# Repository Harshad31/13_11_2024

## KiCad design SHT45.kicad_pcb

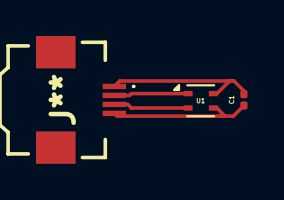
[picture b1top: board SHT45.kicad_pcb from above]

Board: 2 copper layers, 3 parts (0 on the bottom side), 4 nets.

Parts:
C1: 100nF; C_0201_0603Metric
J**: FFC2B3504T
U1: SHT4x; Sensirion_DFN-4_1.5x1.5mm_P0.8mm_SHT4x_NoCentralPad

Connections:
/GND: C1.2, J**.1, U1.4 (VSS)
/SCL: J**.3, U1.2 (SCL)
/SDA: J**.2, U1.1 (SDA)
/VDD: C1.1, J**.4, U1.3 (VDD)

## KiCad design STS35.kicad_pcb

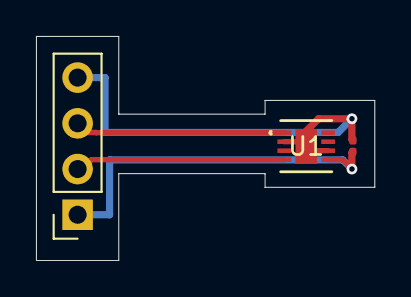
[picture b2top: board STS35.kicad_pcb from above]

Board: 2 copper layers, 18.8 x 12.4 mm, 3 parts (0 on the bottom side), 4 nets.

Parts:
C1: 100nF; C_0201_0603Metric
J2: Conn_01x04_Pin; PinSocket_1x04_P2.54mm_Vertical
U1: STS35-DIS; STS3x-DIS_SEN

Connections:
/GND: C1.2, J2.4, U1.2 (ADDR), U1.6 (NRESET), U1.9 (VSS)
/SCL: J2.2, U1.4 (SCL)
/SDA: J2.3, U1.1 (SDA)
/VDD3.3: C1.1, J2.1, U1.5 (VDD)

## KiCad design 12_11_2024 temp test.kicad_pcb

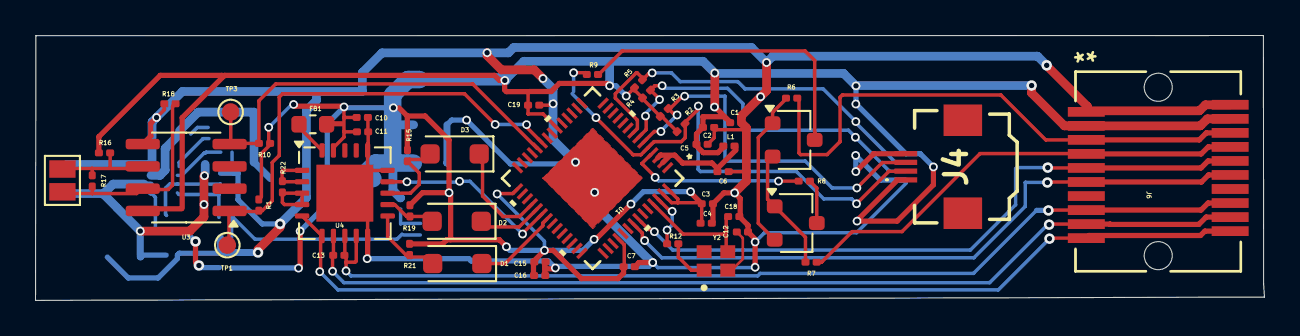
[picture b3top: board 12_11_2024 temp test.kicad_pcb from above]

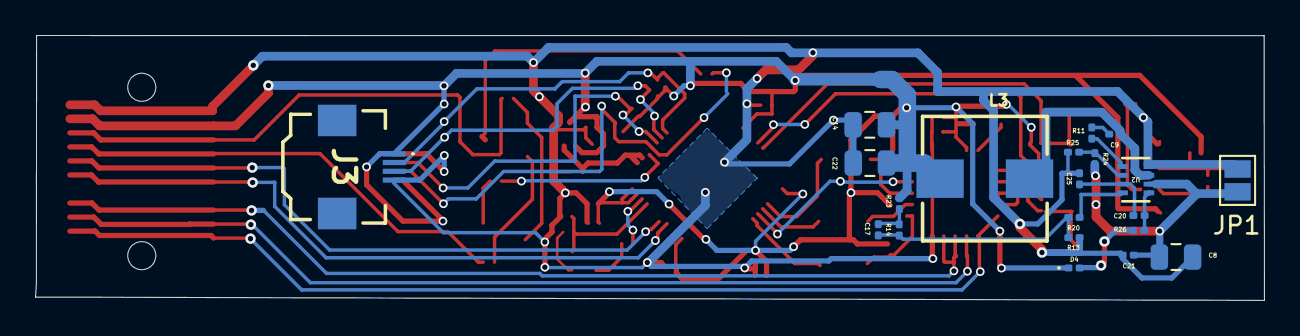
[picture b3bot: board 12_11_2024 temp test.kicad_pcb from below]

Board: 2 copper layers, 70.1 x 15.1 mm, 70 parts (21 on the bottom side), 47 nets.

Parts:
C1, C4, C13: 10uF; C_0201_0603Metric
C2, C3, C9, C16: 1uF; C_0201_0603Metric
C5, C6, C7, C10, C11, C12, C15, C18, C19: 0.1uF; C_0201_0603Metric
C8: 22uF(50V); C_0805_2012Metric
C14, C22: 22µF; C_0805_2012Metric
C17: 10pF; C_0201_0603Metric
C20: 1nF; C_0201_0603Metric
C21: 0.1uF(50V); C_0201_0603Metric
C25: 6.8nF; C_0201_0603Metric
D1, D2, D3: 1N4148W; D_SOD-123F
D4: LED; LED_0201_0603Metric
FB1: 470R; L_0603_1608Metric
J3, J4: FFC2B35-04-T; FFC2B3504T
J6: 10056847-101LF; CONN_10056847-101LF_AMP
JP1, JP2: SolderJumper_2_Open; SolderJumper-2_P1.3mm_Open_Pad1.0x1.5mm
L1: 2.0nH; L_0201_0603Metric
L3: 3.3µH; WE-HCI_7050
Q1, Q2: L8050QLT1G; SC-59
R1, R10: 10K; R_0201_0603Metric
R2, R3, R4, R5, R6, R7, R15, R19, R21: 10k; R_0201_0603Metric
R8, R9: 0R; R_0201_0603Metric
R11: 20R; R_0201_0603Metric
R12: 22R; R_0201_0603Metric
R13: 13K; R_0201_0603Metric
R14: 40.2K; R_0201_0603Metric
R16, R18: 20k; R_0201_0603Metric
R17: 120R; R_0201_0603Metric
R20: 20K; R_0201_0603Metric
R22: 400R; R_0201_0603Metric
R23: 10R; R_0201_0603Metric
R24: 1M; R_0201_0603Metric
R25: NC; R_0201_0603Metric
R26: 65R; R_0201_0603Metric
TP1, TP3: TestPoint; TestPoint_Pad_D1.0mm
U1: ESP32-S3FN8; ESP32 S3FN8_7X7_EXP-
U2: MP2393GTL-P; SOT583_MP2393
U3: THVD1420D; SOIC-8_3.9x4.9mm_P1.27mm
U4: MAX31865xTP; TQFN-20-1EP_5x5mm_P0.65mm_EP3.25x3.25mm
Y2: ECS-400-10-37B2-CKM-TR; XTAL_ECS-400-10-37B2-CKM-TR

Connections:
24V: C8.1, C21.1, JP1.2 (B), R24.1, U2.2 (IN)
/CHIP_PU: R8.2, U1.4 (CHIP_PU)
/CS: D3.1 (K), U1.32 (SPICS0)
/DTR: J6.4, J6.17, R7.1
/FORCE+: J6.10, J6.11, U4.5 (FORCE+), U4.6 (FORCE2)
/GPIO0: J4.2, R2.2, R9.2, U1.5 (GPIO0)
/MISO: U1.34 (SPIQ), U4.14 (SDO)
/MOSI: D1.1 (K), U1.35 (SPID)
/RTDN+: C13.1, J6.9, J6.12, U4.7 (RTDIN+)
/RTDN-: C13.2, J6.8, J6.13, U4.8 (RTDIN-), U4.9 (FORCE-)
/RTS: J6.3, J6.18, R6.1
/RX: J6.5, J6.16, U1.50 (U0RXD)
/RX1: R10.2, TP3.1, U1.24 (GPIO18), U3.4 (DI)
/SCL1: J3.3, R4.2, U1.7 (GPIO2)
/SCLK: D2.1 (K), U1.33 (SPICLK)
/SDA0: J4.3, R3.2, U1.6 (GPIO1)
/SDA1: J3.2, R5.2, U1.8 (GPIO3)
/TX: J6.6, J6.15, U1.49 (U0TXD)
/TX1: R1.2, TP1.1, U1.23 (GPIO17), U3.1 (RO)
/VDD3.3: C1.1, C2.1, C3.1, C4.1, C5.1, C6.1, C7.1, C10.1, C11.1, C14.1, C15.1, C16.1, C19.1, C22.1, D4.1 (K), FB1.1, J3.1, J4.1, J6.2, J6.19, L1.1, L1.2, L3.1, R1.1, R2.1, R3.1, R4.1, R5.1, R10.1, R15.1, R16.1, R19.1, R21.1, R23.1, U1.2 (VDD3P3), U1.3 (VDD3P3), U1.20 (VDD3P3_RTC), U1.29 (VDD_SPI), U1.46 (VDD3P3_CPU), U1.55 (VDDA), U1.56 (VDDA), U3.8 (VCC), U4.19 (DVDD)
/XTAL_N: C18.1, U1.53 (XTAL_N), Y2.3
/XTAL_P: R12.2, U1.54 (XTAL_P)
A: JP2.2 (B), R16.2, R17.1, U3.6 (A)
B: JP2.1 (A), R17.2, R18.1, U3.7 (B)
GND: C1.2, C2.2, C3.2, C4.2, C5.2, C6.2, C7.2, C8.2, C10.2, C11.2, C12.2, C14.2, C15.2, C16.2, C18.2, C19.2, C21.2, C22.2, C25.2, J3.4, J4.4, J6.1, J6.20, JP1.1 (A), R13.1, R18.2, R25.1, U1.57 (GND), U2.4 (GND), U3.5 (GND), U4.10 (GND), U4.15 (DGND), U4.16 (GND), U4.21 (GND)
unnamed: C9.1, R11.2
unnamed: C12.1, Y2.2
unnamed: C17.1, R13.2, R14.1, R20.2
unnamed: C17.2, R14.2, R23.2
unnamed: D1.2 (A), R21.2, U4.11 (SDI)
unnamed: D2.2 (A), R19.2, U4.12 (SCLK)
unnamed: D3.2 (A), R15.2, U4.13 (~CS)
unnamed: D4.2 (A), R26.1
unnamed: Q1.1, Q2.2, R7.2
unnamed: Q1.2, Q2.1, R6.2
unnamed: Q1.3, R8.1
unnamed: Q2.3, R9.1
unnamed: R12.1, Y2.1
unnamed: R11.1, U2.5 (BST)
unnamed: R24.2, R25.2, U2.6 (EN)
unnamed: R20.1, U2.8 (FB)
unnamed: C20.2, R26.2, U2.1 (PG)
unnamed: C20.1, C25.1, U2.7 (SS)
unnamed: C9.2, L3.2, U2.3 (SW)
unnamed: R22.1, U4.1 (BIAS), U4.2 (REFIN+)
unnamed: R22.2, U4.3 (REFIN-), U4.4 (ISENSOR)
unnamed: FB1.2, U4.20 (VDD)

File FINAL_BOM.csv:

Reference,Value,Footprint,Qty,Description,Package
"C1,C4,C13",10uF,Capacitor_SMD:C_0201_0603Metric,3,Unpolarized capacitor,
"C2,C3,C16",1uF,Capacitor_SMD:C_0201_0603Metric,3,Unpolarized capacitor,
"C5,C6,C7,C10,C11,C12,C15,C18,C19",0.1uF,Capacitor_SMD:C_0201_0603Metric,9,Unpolarized capacitor,
C8,22uF(50V),Capacitor_SMD:C_0805_2012Metric,1,Unpolarized capacitor,
C9,1uF(16V),Capacitor_SMD:C_0201_0603Metric,1,Unpolarized capacitor,
"C14,C22",22uF(16V),Capacitor_SMD:C_0805_2012Metric,2,Unpolarized capacitor,
C17,10pF(50V),Capacitor_SMD:C_0201_0603Metric,1,Unpolarized capacitor,
C20,1nF(50V),Capacitor_SMD:C_0201_0603Metric,1,Unpolarized capacitor,
C21,0.1uF(50V),Capacitor_SMD:C_0201_0603Metric,1,Unpolarized capacitor,
C25,6.8nF(50V),Capacitor_SMD:C_0201_0603Metric,1,Unpolarized capacitor,
"D1,D2,D3",1N4148W,Diode_SMD:D_SOD-123F,3,"75V 0.15A Fast Switching Diode, SOD-123",
D4,LED,LED_SMD:LED_0201_0603Metric,1,Light emitting diode,
FB1,470R,Inductor_SMD:L_0603_1608Metric,1,Ferrite bead,
"J3,J4",FFC2B35-04-T,KiCad:FFC2B3504T,2,FFC & FPC Connectors .5mm SideEntry Flat Flex Cbl Conn 4P Sn,
J6,10056847-101LF,footprints14:CONN_10056847-101LF_AMP,1,,
L1,2.0nH,Inductor_SMD:L_0201_0603Metric,1,Inductor,
L3,3.3?H,HCI:WE-HCI_7050,1,Inductor,
"Q1,Q2",L8050QLT1G,Package_TO_SOT_SMD:SC-59,2,,
"R1,R10",10K,Resistor_SMD:R_0201_0603Metric,2,Resistor,
"R2,R3,R4,R5,R6,R7,R15,R19,R21",10k,Resistor_SMD:R_0201_0603Metric,9,Resistor,
"R8,R9",0R,Resistor_SMD:R_0201_0603Metric,2,Resistor,
R11,20R,Resistor_SMD:R_0201_0603Metric,1,Resistor,
R12,22R,Resistor_SMD:R_0201_0603Metric,1,Resistor,
R13,13K,Resistor_SMD:R_0201_0603Metric,1,Resistor,
R14,40.2K,Resistor_SMD:R_0201_0603Metric,1,Resistor,
"R16,R18",20k,Resistor_SMD:R_0201_0603Metric,2,Resistor,
R17,120R,Resistor_SMD:R_0201_0603Metric,1,Resistor,
R20,20K,Resistor_SMD:R_0201_0603Metric,1,Resistor,
R22,400R,Resistor_SMD:R_0201_0603Metric,1,Resistor,
R23,10R,Resistor_SMD:R_0201_0603Metric,1,Resistor,
R24,1M,Resistor_SMD:R_0201_0603Metric,1,Resistor,
R25,NC,Resistor_SMD:R_0201_0603Metric,1,Resistor,
R26,65R,Resistor_SMD:R_0201_0603Metric,1,Resistor,
"TP1,TP3",TestPoint,TestPoint:TestPoint_Pad_D1.0mm,2,test point,
U1,ESP32-S3FN8,digikey-footprints:ESP32 S3FN8_7X7_EXP-,1,,
U2,MP2393GTL-P,footprints12:SOT583_MP2393,1,,
U3,THVD1420D,Package_SO:SOIC-8_3.9x4.9mm_P1.27mm,1,"Half duplex RS-485/RS-422, 12 Mbps, 3V - 5.5V supply, ?12kV electro-static discharge (ESD) protection, with receiver/driver enable, 32 receiver drive capacity, SOIC-8",
U4,MAX31865xTP,Package_DFN_QFN:TQFN-20-1EP_5x5mm_P0.65mm_EP3.25x3.25mm,1,"RTD-to-Digital Converter, TQFN-20",
Y2,ECS-400-10-37B2-CKM-TR,digikey-footprints:XTAL_ECS-400-10-37B2-CKM-TR,1,,
